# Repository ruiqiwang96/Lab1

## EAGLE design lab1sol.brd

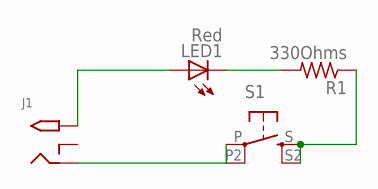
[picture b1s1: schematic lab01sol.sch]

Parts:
J1: 2.1MMJACKTHM; PJ-102A
LED1: Red; LED5MM
R1: 330Ohms; RESAD1160W55L680D260_HS
S1: BUTTON-TACTILE-SQUARE; BUTTON-TACTILE-SQUARE-ADAFRUIT1010

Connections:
unnamed: LED1.K (C), R1.2
unnamed: R1.1, S1.S, S1.S2 (S1)
unnamed: J1.RING, S1.P, S1.P2 (P1)
unnamed: J1.TIP, LED1.A

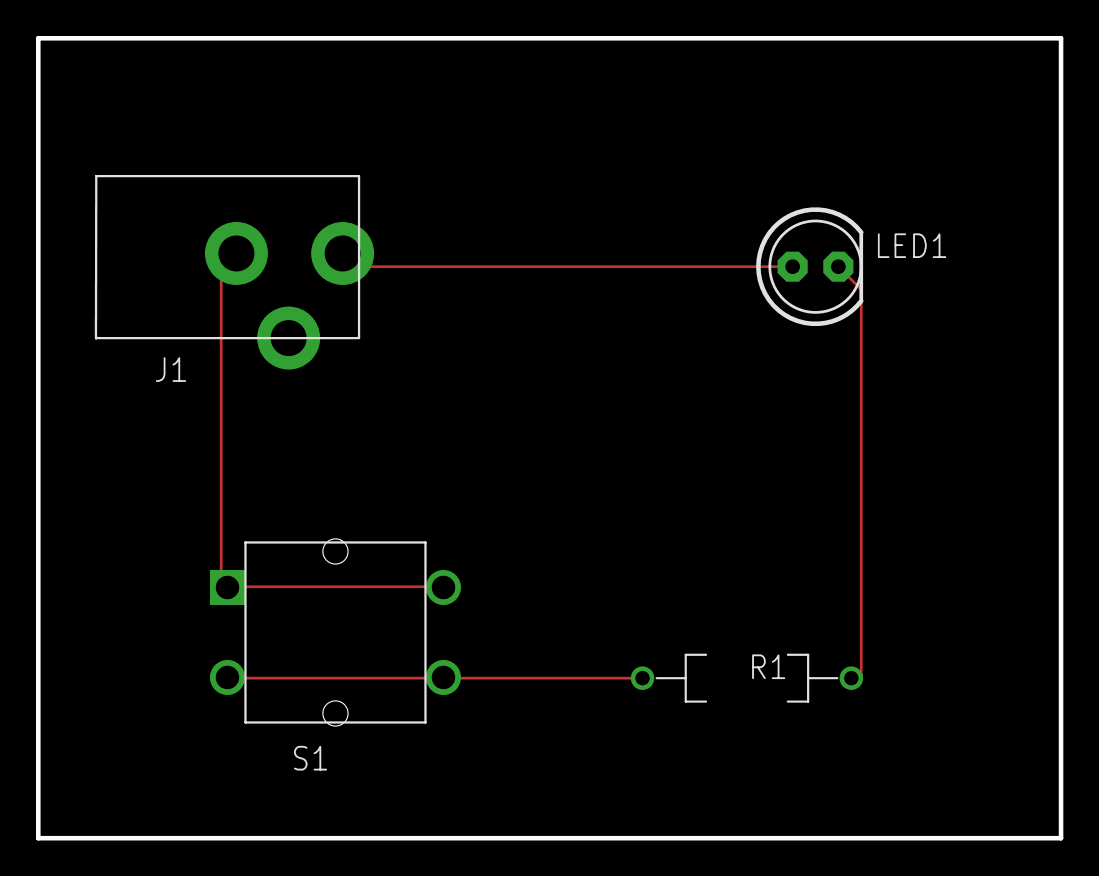
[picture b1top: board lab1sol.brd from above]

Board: 2 copper layers, 56.8 x 44.4 mm, 4 parts (0 on the bottom side), 4 nets.
